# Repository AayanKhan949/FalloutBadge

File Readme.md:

This is basically a simple pcb that just The LDR senses the light level. Depending on the surrounding brightness..
It just 
1) Turn the DC motor on or off
2) Light one or both LEDs to indicate the circuit's state.
3) The push button likely acts as a manual trigger, enable switch, or reset, though its exact function can't be confirmed from the PCB layout alone because the PCB file doesn't contain the circuit logic.

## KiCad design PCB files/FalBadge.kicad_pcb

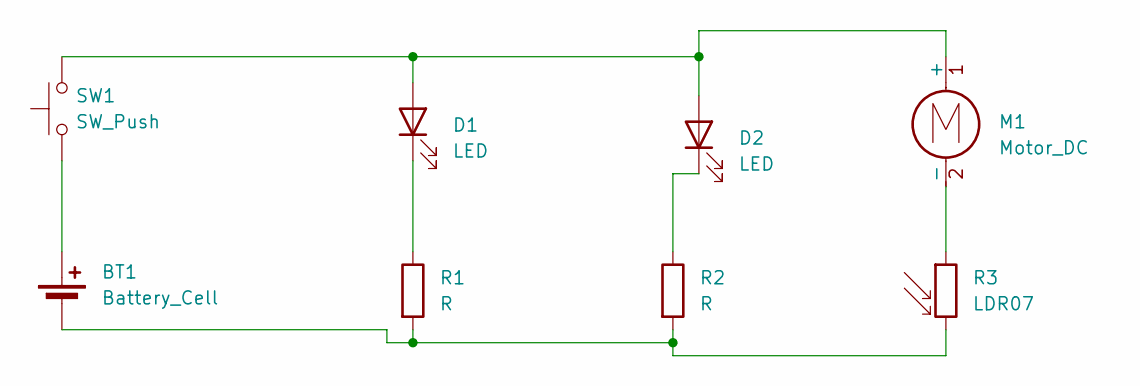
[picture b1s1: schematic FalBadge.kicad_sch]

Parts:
BT1: Battery_Cell; BatteryHolder_Keystone_3034_1x20mm
D1, D2: LED; LED_D5.0mm
M1: Motor_DC; PinHeader_1x02_P2.54mm_Vertical
R1, R2: R; R_Axial_DIN0207_L6.3mm_D2.5mm_P7.62mm_Horizontal
R3: LDR07; R_LDR_5.1x4.3mm_P3.4mm_Vertical
SW1: SW_Push; SW_PUSH_6mm

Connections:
unnamed: BT1.1 (+), SW1.1
unnamed: BT1.2 (-), R1.2, R2.2, R3.2
unnamed: D1.2 (A), D2.2 (A), M1.1 (+), SW1.2
unnamed: D1.1 (K), R1.1
unnamed: D2.1 (K), R2.1
unnamed: M1.2 (-), R3.1

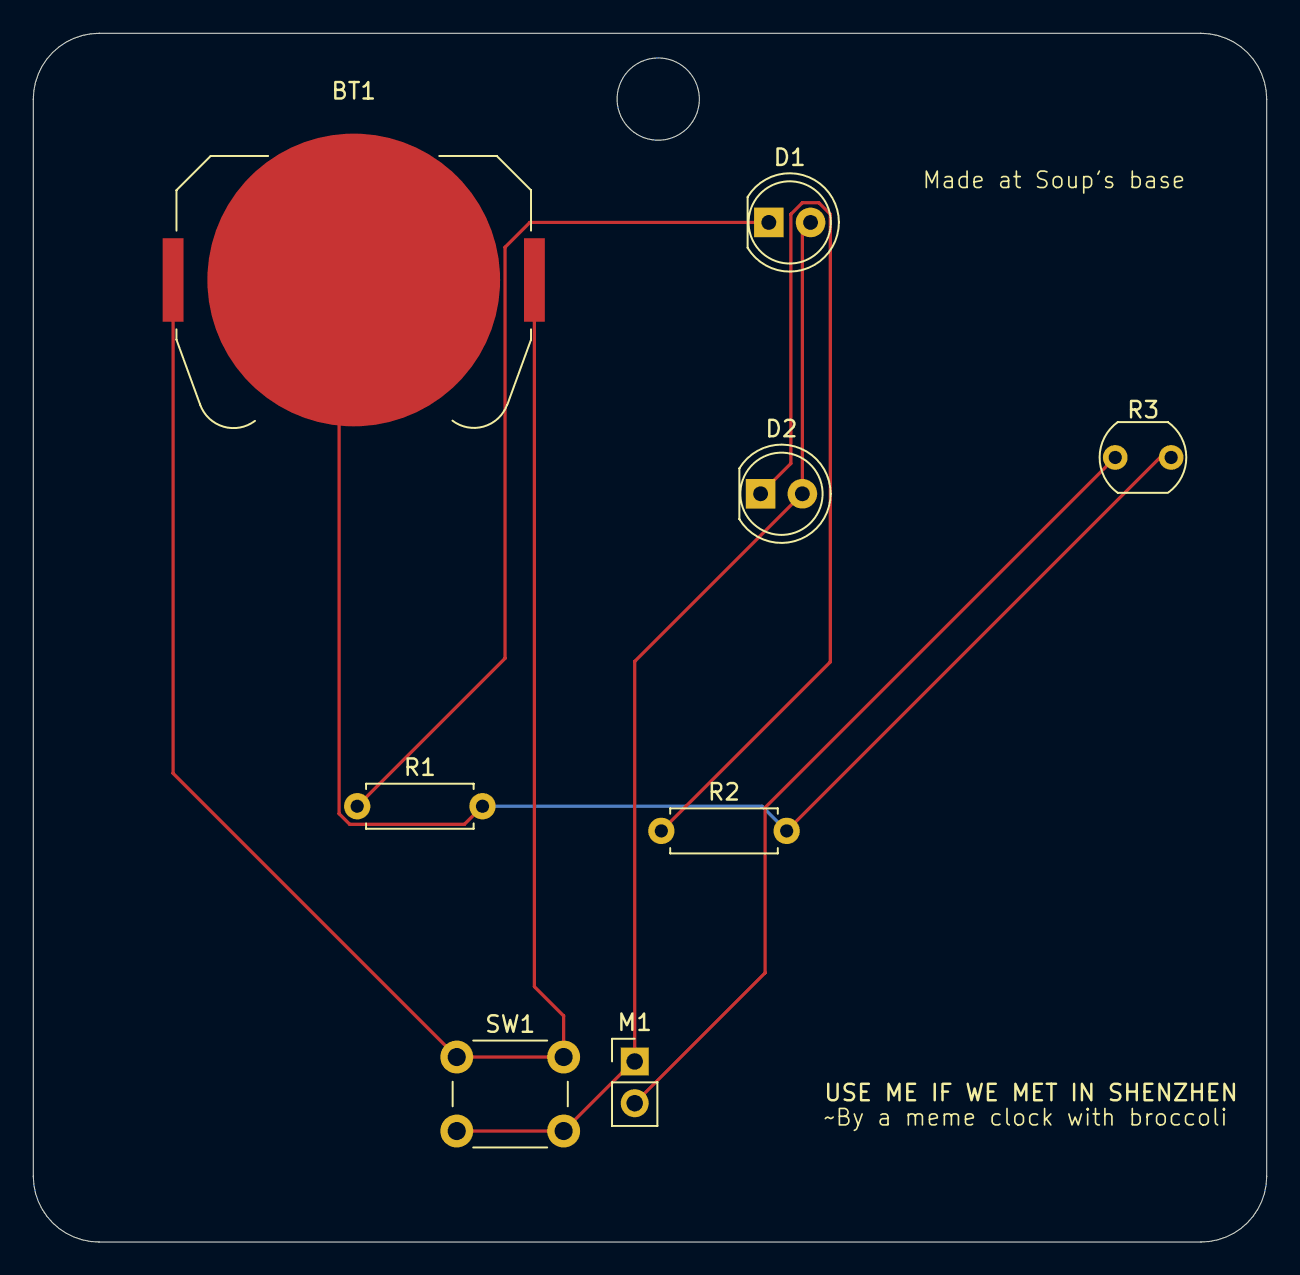
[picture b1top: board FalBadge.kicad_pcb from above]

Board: 2 copper layers, 75.0 x 73.5 mm, 8 parts (0 on the bottom side), 6 nets.
